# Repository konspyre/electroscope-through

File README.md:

# electroscope (through-hole edition)

This is a similar board to the [surface mount electroscope](https://github.com/davidk/electroscope) but is easier (or harder, depending on your manufacturing viewpoint) to assemble and source parts for.

<a href="https://oshpark.com/shared_projects/JK9TLh1I"></img></a>

### Bill of Materials

This BOM specifies the amount needed for _one_ board. Parts have been translated from their surface mount equivalents.

| Quantity | Description | Digikey Part Number | Board Placement |
| -------- | ----------- | ----------- | --------------- |
| 3        | 2N3906      | [2N3906D26ZCT-ND](https://www.digikey.com/products/en?keywords=2N3906D26ZCT-ND) | Left (label: PNP) |
| 3 	   | 2N3904	 | [2N3904FS-ND](https://www.digikey.com/products/en?keywords=2N3904FS-ND) | Right (label: NPN) |
| 2        | 100 ohm resistor | [100QBK-ND](https://www.digikey.com/product-detail/en/CFR-25JB-52-100R/100QBK-ND/246) | Bottom (label: 100 ohm) |
| 2        | 100k ohm resistor | [100KQBK-ND](https://www.digikey.com/products/en?keywords=100kQBK-ND) | Middle (label: 100k ohm) |
| 2	   | 1M ohm resistor | [1.0MQBK-ND](https://www.digikey.com/product-detail/en/yageo/CFR-25JB-52-1M/1.0MQBK-ND/99) | Top (label: 1M ohm) |

### Battery connector

| Quantity | Description | Digikey Part Number | Board Placement |
| -------- | ----------- | ----------- | --------------- |
| 1        | 9v through-hole battery snap - long | [36-968-ND](https://www.digikey.com/product-detail/en/keystone-electronics/968/36-968-ND/151577) | 9V terminals (verify before soldering by attaching to a 9V battery -- reworking afterwards is difficult without specialized tools/materials) |

or

| Quantity | Description | Digikey Part Number | Board Placement |
| -------- | ----------- | ----------- | --------------- |
| 1        | 9v through-hole battery snap - short | [36-967-ND](https://www.digikey.com/product-detail/en/keystone-electronics/967/36-967-ND/2745660) |  9V terminals (verify before soldering by attaching to a 9V battery -- reworking afterwards is difficult without specialized tools/materials) |

#### LEDs

| Quantity | Description | Digikey Part Number | Board Placement |
| -------- | ----------- | ----------- | --------------- |
| 2        | 3mm LEDs | (Red: [160-1704-ND](http://www.digikey.com/product-search/en?vendor=0&keywords=160-1704-ND) / Green: [160-1958-ND](http://www.digikey.com/product-search/en?vendor=0&keywords=160-1958-ND) | Bottom (verify orientation before soldering!) |

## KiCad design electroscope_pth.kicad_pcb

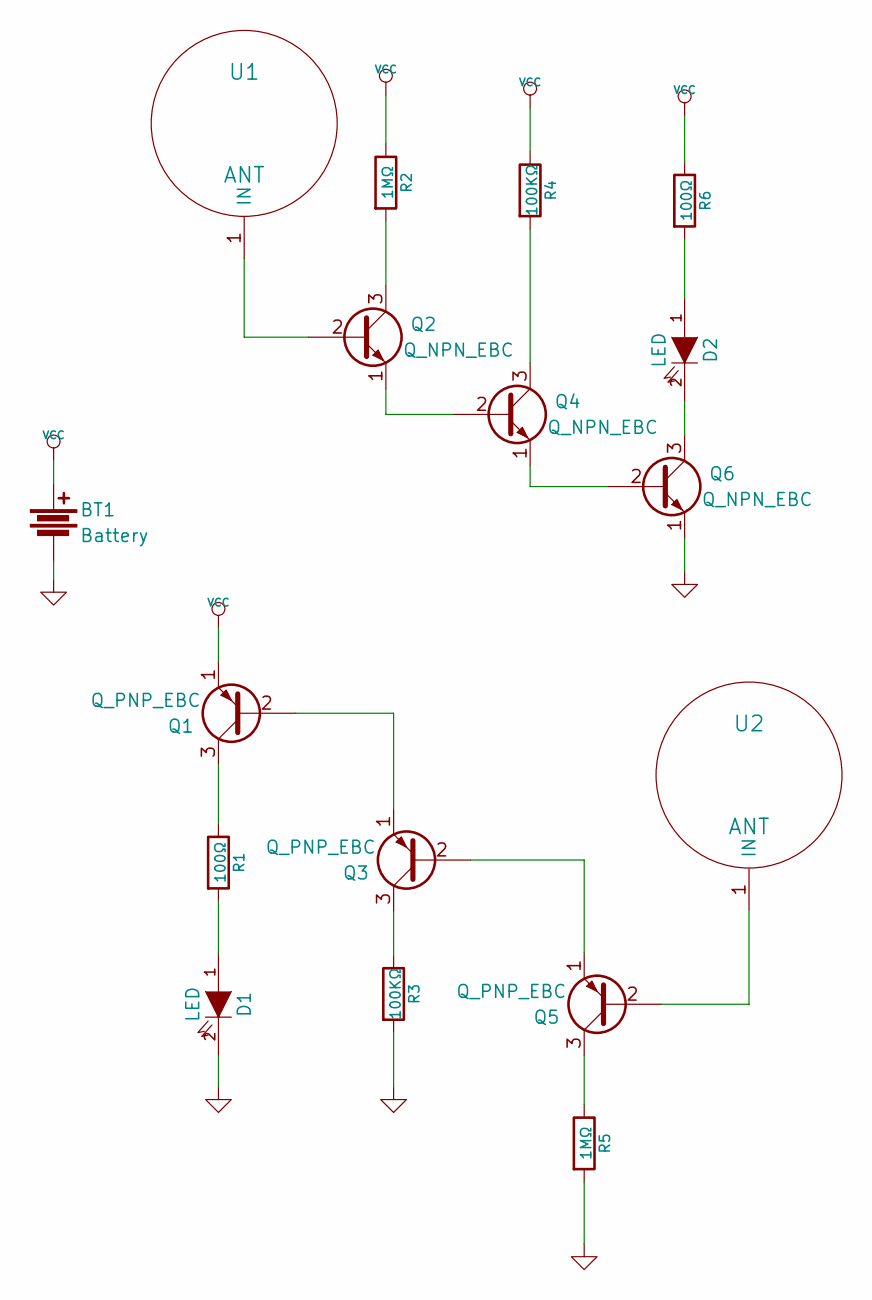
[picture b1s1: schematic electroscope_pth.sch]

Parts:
BT1: Battery
D1, D2: LED
Q1, Q3, Q5: Q_PNP_EBC
Q2, Q4, Q6: Q_NPN_EBC
R1, R6: 100Ω
R2, R5: 1MΩ
R3, R4: 100KΩ
U1, U2: ANT

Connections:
GND: BT1.2, D1.2 (K), Q6.1 (E), R3.2, R5.2
unnamed: D1.1 (A), R1.2
unnamed: D2.1 (A), R6.2
unnamed: D2.2 (K), Q6.3 (C)
unnamed: Q1.2 (B), Q3.1 (E)
unnamed: Q1.3 (C), R1.1
unnamed: Q2.1 (E), Q4.2 (B)
unnamed: Q2.2 (B), U1.1
unnamed: Q2.3 (C), R2.2
unnamed: Q3.2 (B), Q5.1 (E)
unnamed: Q3.3 (C), R3.1
unnamed: Q4.1 (E), Q6.2 (B)
unnamed: Q4.3 (C), R4.2
unnamed: Q5.2 (B), U2.1
unnamed: Q5.3 (C), R5.1
VCC: BT1.1, Q1.1 (E), R2.1, R4.1, R6.1

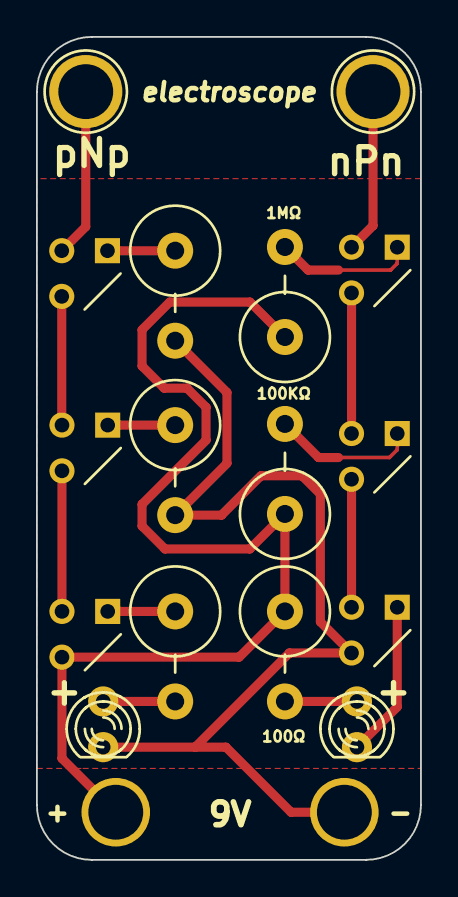
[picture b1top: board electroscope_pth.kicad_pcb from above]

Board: 2 copper layers, 21.3 x 45.7 mm, 17 parts (0 on the bottom side), 16 nets.

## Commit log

2015-09-08 add gitignore
2015-09-08 Add libs, and schematic
2015-09-09 Add pcb backup to .gitignore
2015-09-09 General placement down
2015-09-09 Add untracked files
2015-09-09 Ready to mill
2015-09-09 Add isolated plane @ bottom 3/4ths or so of board
2019-03-13 Re-route PCB with centered dimensions and rework footprint silkscreens
2019-03-14 Add re-routing
2019-03-14 Route to the edges of the board
2019-03-14 Add a more up-to-date gitignore for KiCad
2019-03-14 Add updated electroscope schematic
2019-03-14 Add new gerbers based on board re-route
2019-03-14 Add README with render
2019-03-15 More rounding and compaction
2019-03-15 Update electroscope image
2019-03-16 electroscope: Remove flood fill overlap
2019-03-16 electroscope: Add an updated render
2019-03-16 electroscope: silkscreen improvements
2019-03-21 Add current electroscope
2019-04-04 Center 1M silk
2019-09-07 README: Change battery connector
2020-07-09 Add direct fabrication link
2020-08-23 README: Placement instructions
2020-12-24 README: Fix badge
2021-04-26 Add picture of assembled electroscope
